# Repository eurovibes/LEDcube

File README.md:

<!-- SPDX-FileCopyrightText: 2021 Benedikt Spranger <b.spranger@linutronix.de> -->
<!-- SPDX-License-Identifier: CERN-OHL-S-2.0 -->

# LEDcube -  Olimex STMP157-OLinuXino-LIME2 Sensor and Motor shield

## License rules

LEDcube is provided under the terms of the CERN-OHL-S license
version 2 as provided in the LICENSES/CERN-OHL-S-2.0 file.

Instead of adding license boilerplates to the individual files,
LEDcube uses SPDX license identifiers, which are machine parseable
and considered legaly equivalent.

The SPDX license identifier in LEDcube shall be added at the first
possible line in a file which can contain a comment. This is normally the
first line except for scripts. Scripts require the #!PATH_TO_INTERPRETER tag
in the first line; place the SPDX identifier into the second line.

The SPDX license identifier is added in form of a comment.

## Copyright and License

> Copyright Benedikt Spranger 2021.
> This source describes Open Hardware and is licensed under the CERNOHL-S v2.
> You may redistribute and modify this source and make products using it
> under the terms of the CERN-OHL-S v2 (https://ohwr.org/cern ohl s v2.txt ).
> This source is distributed WITHOUT ANY EXPRESS OR IMPLIED WARRANTY, INCLUDING
> OF MERCHANTABILITY, SATISFACTORY QUALITY AND FITNESS FOR A PARTICULAR PURPOSE.
> Please see the CERN-OHL-S v2 for applicable conditions.
> Source location: https://github.com/eurovibes/LEDcube
> As per CERN-OHL-S v2 section 4, should You produce hardware based
> on this source, You must where practicable maintain the Source Location
> visible on the external case of the LEDcube or other products you
> make using this source.

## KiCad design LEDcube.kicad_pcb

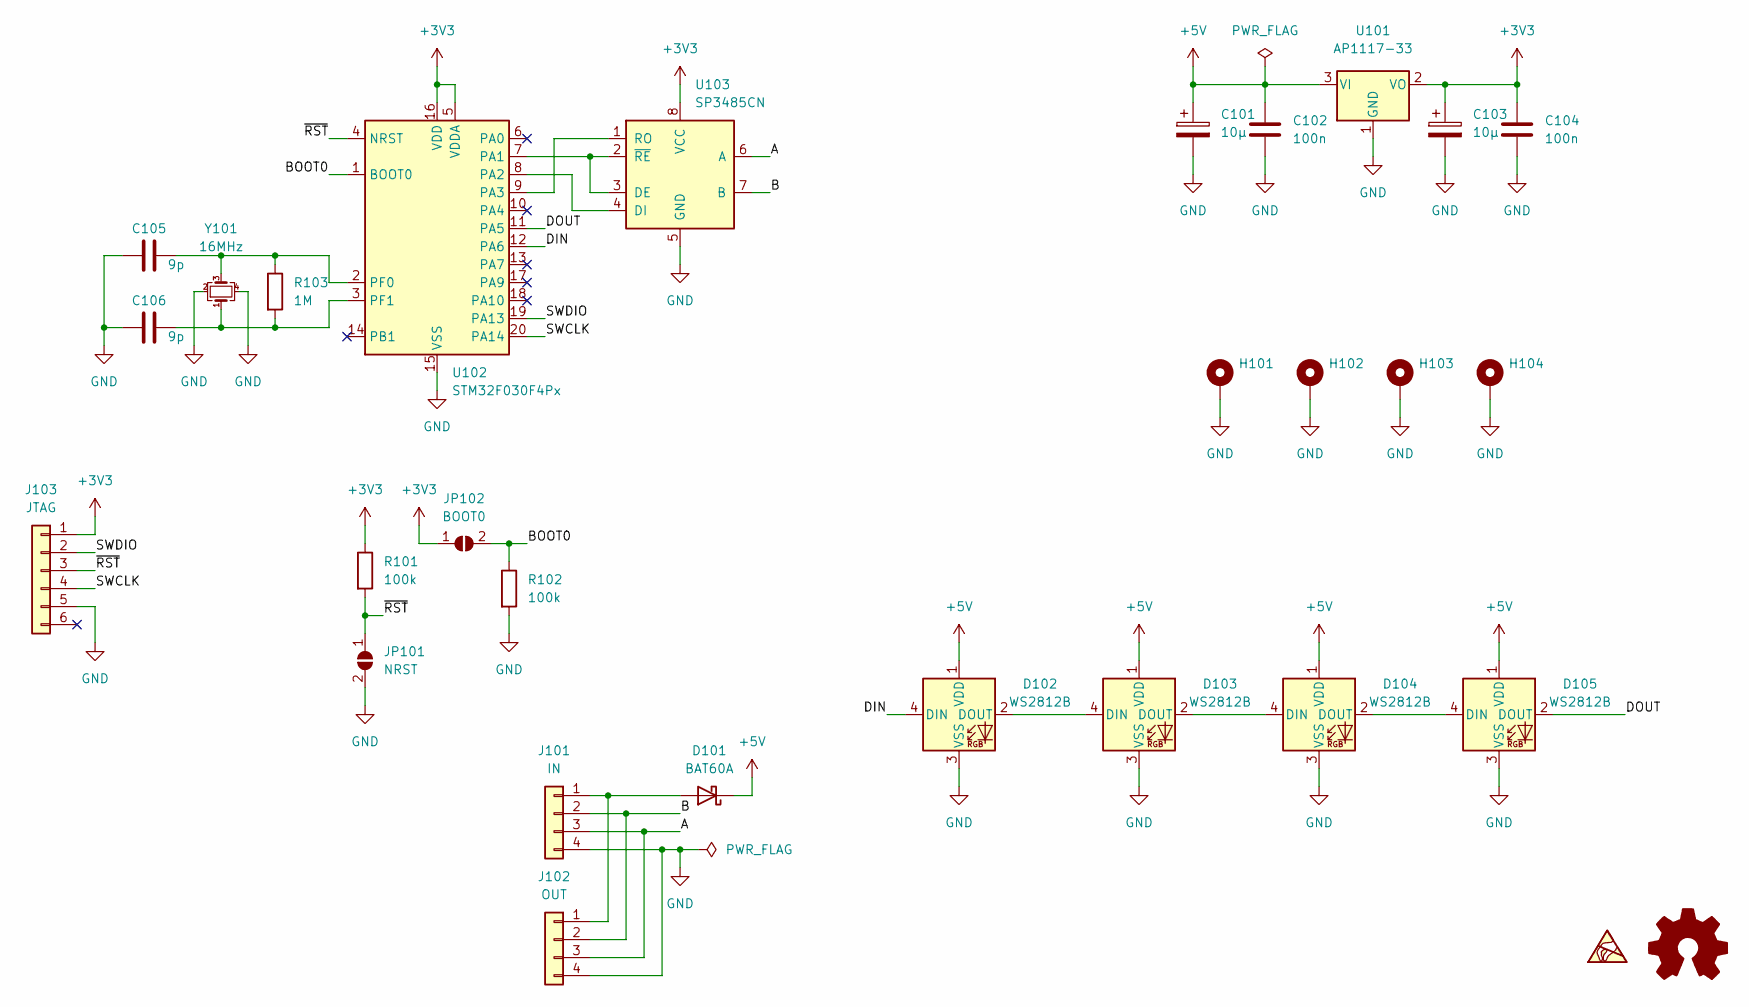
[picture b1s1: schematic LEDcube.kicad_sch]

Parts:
C101, C103: 10µ; CP_EIA-3216-18_Kemet-A; ManuPart# TAJA106K016RNJ; LCSC# C7171
C102, C104: 100n; C_0402_1005Metric; ManuPart# CL05B104KO5NNNC; LCSC# C1525
C105, C106: 9p; C_0402_1005Metric; ManuPart# CL05C100JB5NNNC; LCSC# C32949
D101: BAT60A; D_SOD-323; ManuPart# BAT60AE6327H; LCSC# C520634
D102, D103, D104, D105: WS2812B; LED_WS2812B_PLCC4_5.0x5.0mm_P3.2mm; ManuPart# WS2812B-B/W; LCSC# C2761795
H101, H102, H103, H104: MountingHole_3.2mm_M3_ISO14580_Pad
J101: IN; PinHeader_1x04_P2.54mm_Vertical
J102: OUT; PinHeader_1x04_P2.54mm_Vertical
J103: JTAG; Tag-Connect_TC2030-IDC-FP_2x03_P1.27mm_Vertical
JP101: NRST; SolderJumper-2_P1.3mm_Open_RoundedPad1.0x1.5mm
JP102: BOOT0; SolderJumper-2_P1.3mm_Open_RoundedPad1.0x1.5mm
R101, R102: 100k; R_0402_1005Metric
R103: 1M; R_0402_1005Metric
U101: AP1117-33; SOT-223-3_TabPin2; ManuPart# AP1117E33G-13; LCSC# C108785
U102: STM32F030F4Px; TSSOP-20_4.4x6.5mm_P0.65mm; ManuPart# STM32F030F4P6TR; LCSC# C89040
U103: SP3485CN; SOIC-8_3.9x4.9mm_P1.27mm; ManuPart# SP3485EN-L/TR; LCSC# C8963
Y101: 16MHz; Crystal_SMD_3225-4Pin_3.2x2.5mm; ManuPart# X322516MLB4SI; LCSC# C13738

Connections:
+3V3: C103.1, C104.2, J103.1, JP102.1 (A), R101.1, U101.2 (VO), U102.5 (VDDA), U102.16 (VDD), U103.8 (VCC)
+5V: C101.1, C102.2, D101.1 (K), D102.1 (VDD), D103.1 (VDD), D104.1 (VDD), D105.1 (VDD), U101.3 (VI)
/A: J101.3, J102.3, U103.6 (A)
/B: J101.2, J102.2, U103.7 (B)
/BOOT0: JP102.2 (B), R102.1, U102.1 (BOOT0)
/DIN: D102.4 (DIN), U102.12 (PA6)
/DOUT: D105.2 (DOUT), U102.11 (PA5)
/SWCLK: J103.4, U102.20 (PA14)
/SWDIO: J103.2, U102.19 (PA13)
/~RST: J103.3, JP101.1 (A), R101.2, U102.4 (NRST)
GND: C101.2, C102.1, C103.2, C104.1, C105.1, C106.1, D102.3 (VSS), D103.3 (VSS), D104.3 (VSS), D105.3 (VSS), H101.1, H102.1, H103.1, H104.1, J101.4, J102.4, J103.5, JP101.2 (B), R102.2, U101.1 (GND), U102.15 (VSS), U103.5 (GND), Y101.2, Y101.4
unnamed: C105.2, R103.1, U102.2 (PF0), Y101.3
unnamed: C106.2, R103.2, U102.3 (PF1), Y101.1
unnamed: D101.2 (A), J101.1, J102.1
unnamed: D102.2 (DOUT), D103.4 (DIN)
unnamed: D103.2 (DOUT), D104.4 (DIN)
unnamed: D104.2 (DOUT), D105.4 (DIN)
unnamed: U102.7 (PA1), U103.2 (~RE), U103.3 (DE)
unnamed: U102.8 (PA2), U103.4 (DI)
unnamed: U102.9 (PA3), U103.1 (RO)

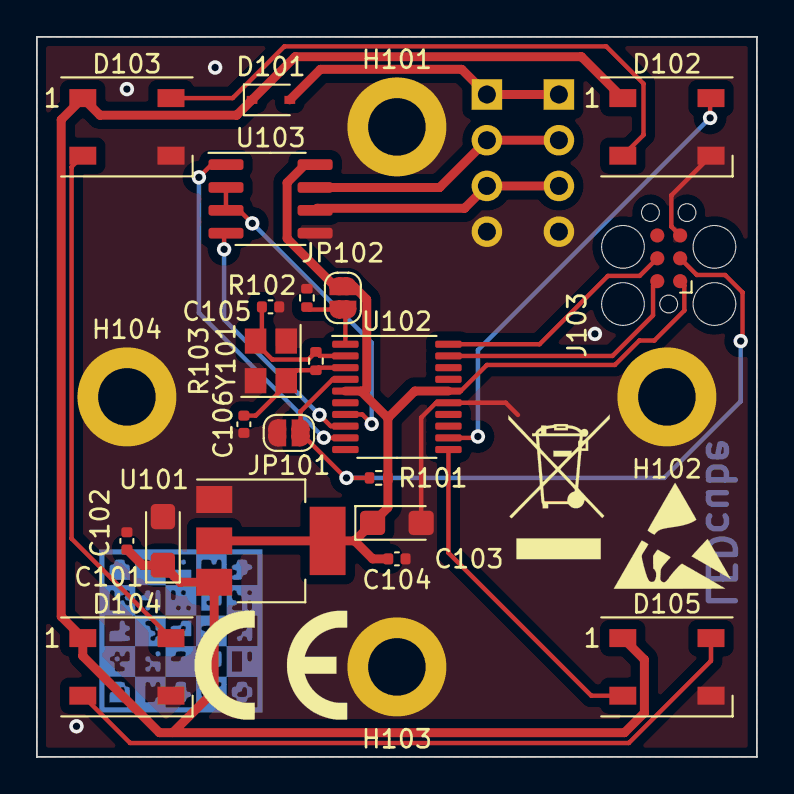
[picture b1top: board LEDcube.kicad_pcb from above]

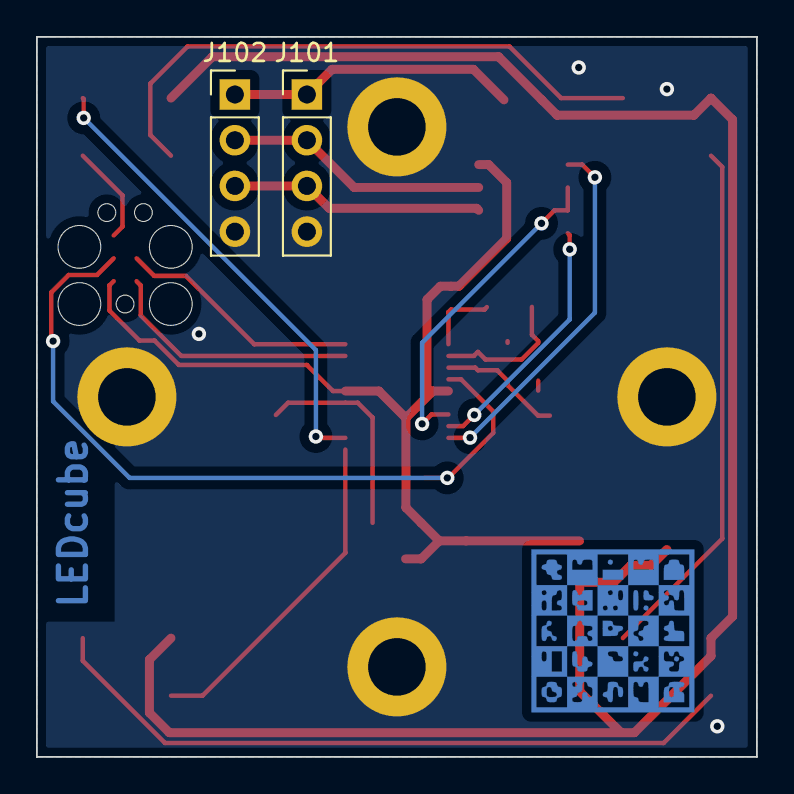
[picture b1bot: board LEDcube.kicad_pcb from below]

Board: 2 copper layers, 40.0 x 40.0 mm, 31 parts (3 on the bottom side), 20 nets.

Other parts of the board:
SYM1: LOGO
SYM2: WEEE-Logo_5.6x8mm_SilkScreen
SYM3: ESD-Logo_6.6x6mm_SilkScreen
SYM4: CE-Logo_8.5x6mm_SilkScreen

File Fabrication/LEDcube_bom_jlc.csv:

"Comment","Designator","Footprint","LCSC Part #"
"9p","C105,C106","C_0402_1005Metric","C32949"
"100n","C102,C104","C_0402_1005Metric","C1525"
"10µ","C101,C103","CP_EIA-3216-18_Kemet-A","C7171"
"BAT60A","D101","D_SOD-323","C520634"
"WS2812B","D102,D103,D104,D105","LED_WS2812B_PLCC4_5.0x5.0mm_P3.2mm","C2761795"
"AP1117-33","U101","SOT-223-3_TabPin2","C108785"
"SP3485CN","U103","SOIC-8_3.9x4.9mm_P1.27mm","C8963"
"STM32F030F4Px","U102","TSSOP-20_4.4x6.5mm_P0.65mm","C89040"
"16MHz","Y101","Crystal_SMD_3225-4Pin_3.2x2.5mm","C13738"

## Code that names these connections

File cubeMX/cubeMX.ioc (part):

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Mcu.Name=STM32F030F4Px
Mcu.Package=TSSOP20
Mcu.UserName=STM32F030F4Px
PA1.Mode=Hardware Flow Control (RS485)
PA1.Signal=USART1_DE
PA13.Mode=Serial_Wire
PA13.Signal=SYS_SWDIO
PA14.Mode=Serial_Wire
PA14.Signal=SYS_SWCLK
PA2.Mode=Asynchronous
PA2.Signal=USART1_TX
PA3.Mode=Asynchronous
PA3.Signal=USART1_RX
PA4.GPIOParameters=GPIO_Label
PA4.GPIO_Label=DIN
PA4.Signal=GPIO_Input
PA6.Signal=S_TIM3_CH1
PF0-OSC_IN.Mode=HSE-External-Oscillator
PF0-OSC_IN.Signal=RCC_OSC_IN
PF1-OSC_OUT.Mode=HSE-External-Oscillator
PF1-OSC_OUT.Signal=RCC_OSC_OUT
RCC.HSE_VALUE=16000000
RCC.SYSCLKFreq_VALUE=48000000
RCC.SYSCLKSource=RCC_SYSCLKSOURCE_PLLCLK
board=custom

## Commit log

2022-05-22 Initial
2022-05-23 Add software
2022-05-23 Initial gh-pages commit
2022-05-23 Deploying to gh-pages from @ eurovibes/LEDcube@76d650e751ab3897b6da312312fd24e9727ce052 🚀
2022-05-25 enclosure: Add cube connection element
2022-08-22 Crystal related fixes
2022-08-22 enclosure rework to fit JLCPCB requirements
2022-08-22 Always run actions on push to master
2022-08-22 Do not ignore changes to github actions
2022-08-22 Use KiBot v1
2022-08-22 Deploying to gh-pages from @ eurovibes/LEDcube@a7234f0d9a771873ee846fc7fcf68f8b4e66b4fe 🚀

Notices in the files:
LEDcube.kicad_sch:
This work is licensed under the CERN-OHL-S v2
